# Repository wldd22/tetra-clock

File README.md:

# Tetra Clock

A custom alarm clock loosely based on the Blare guide.

## Details
PCB made using **KiCAD**<br>
Firmware uses **CircuitPython**

This PCB is a simple alarm clock display I designed to show the date and time, and set alarms.

- **Microcontroller**: XIAO ESP32-S3
- **Display**: 0.91 inch 128x32 OLED display (SSD1306 driver)
- **Sound**: 3V Active Electromagnetic Buzzer
- **Input**: Capacitive touchpads

**Features**:
- **ISO 8601 timestamp** datetime display
- Set **alarm time**
- **Alarm** enabled toggle
- **Snooze** enabled toggle

## About
When I saw [Mitxela's Precision Clock](https://mitxela.com/projects/precision_clock_mk_iv),
I was inspired to design a custom clock myself. I wanted mine to be much more compact, like
something you could carry around in a pocket, but that still looked cool and worked well.
I used capacitive pads because it's an easy way I've found to make button inputs that, one,
don't require any extra components, and two, are as compact as possible, being just as slim
as the board itself.

This project was originally made for week 1 (PCB week) of Hack Club's Half Life. The idea and some of
the components used were based on the [Blare guide](https://blare.hackclub.com/docs/getting-started),
but the actual design and the firmware was created from scratch by me.

## Setup
1. **Obtain hardware** - Buy [the **components**](BOM.csv) and get the **PCB** fabricated ([gerber](/production/gerber/gerber.zip)).
2. **Solder parts** - Using pin headers where necessary, solder the **microcontroller**, **buzzer**, and **display** onto the board.
3. **Install CircuitPython** - Use the [CircuitPython guide for the XIAO ESP32S3](https://wiki.seeedstudio.com/xiao_esp32s3_project_circuitpython/) to install it onto the board.
4. **Upload firmware** - Use the same guide to upload [the firmware](/firmware/code.py) to the board.

## Images

### Schematic

### PCB

## BOM

Item  | Description  | Quantity  | Source  | Cost  | Amount
--- | --- | --- | --- | --- | ---
Seeed Studio XIAO ESP32-S3  |  Microcontroller  |  1  |  [Robu](https://robu.in/product/seeed-studio-xiao-esp32s3-2-4ghz-wifi-ble-5-0/)  |  $12.00  |  $12.00
0.91 inch 128x32 Blue OLED Display Module  |  OLED Screen  |  1  |  [Robu](https://robu.in/product/0-91-inch-128x32-i2c-iic-serial-blue-oled-lcd-display-module/)  |  $2.20  |  $2.20
PCB  |  The board  |  1  |  [JLCPCB](https://jlcpcb.com/)  |  $4.00  |  $4.00
1X20P Machined Pin Header  |  Pin headers for the MCU and display  |  1  |  [Robu](https://robu.in/product/361030120sg111901-jiln-2-54x3-0machined-pin-header-1x20p-180-l11-96-upper-pinpoint0-60-bottom-pinpoint0-50-au1u-pps/)  |  $0.20  |  $0.20
3V Active Electromagnetic Buzzer  |  Buzzer  |  1  |  [Robu](https://robu.in/product/3v-active-electromagnetic-buzzer-pack-of-5/)  |  $0.25  |  $0.25
Estimated total shipping  |  -  |  1  |  -  |  -  |  $10.00
TOTAL  |  |  |  |  |  $28.65

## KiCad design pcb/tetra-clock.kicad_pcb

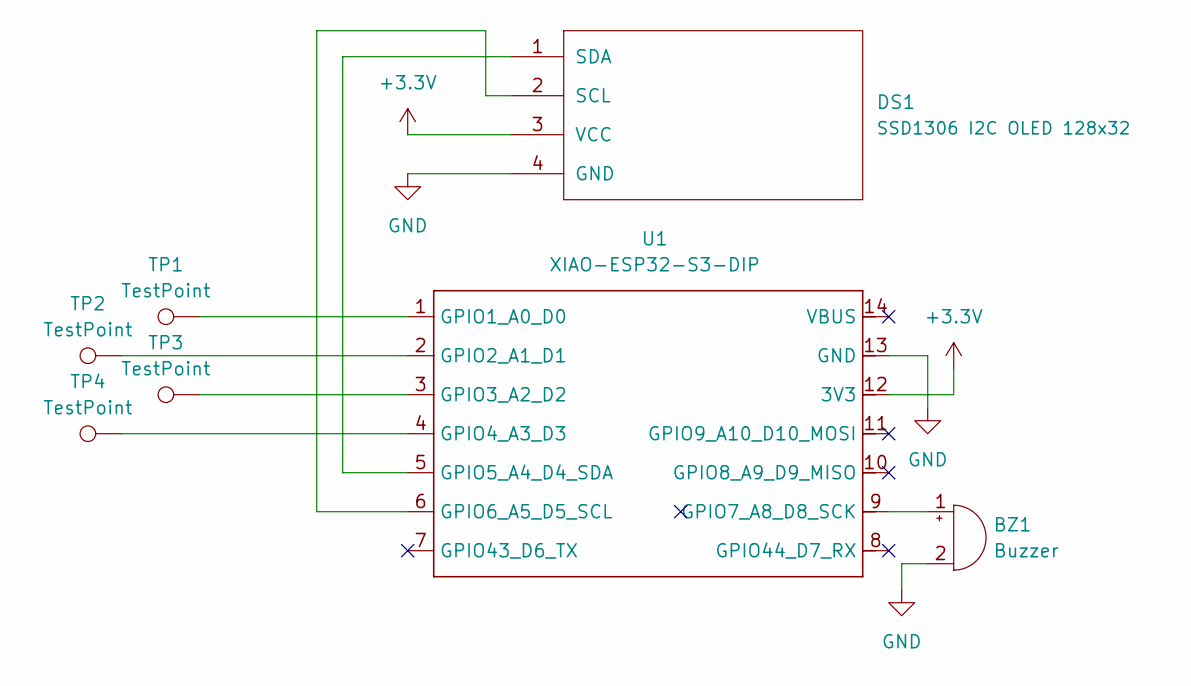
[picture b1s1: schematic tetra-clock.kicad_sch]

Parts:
BZ1: Buzzer; Buzzer_12x9.5RM7.6
DS1: SSD1306 I2C OLED 128x32
TP1, TP2, TP3, TP4: TestPoint; CAP_CIRCLE_PAD
U1: XIAO-ESP32-S3-DIP

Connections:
+3.3V: DS1.3 (VCC), U1.12 (3V3)
GND: BZ1.2 (-), DS1.4 (GND), U1.13 (GND)
unnamed: BZ1.1 (+), U1.9 (GPIO7_A8_D8_SCK)
unnamed: DS1.2 (SCL), U1.6 (GPIO6_A5_D5_SCL)
unnamed: DS1.1 (SDA), U1.5 (GPIO5_A4_D4_SDA)
unnamed: TP1.1 (1_1), U1.1 (GPIO1_A0_D0)
unnamed: TP2.1 (1_1), U1.2 (GPIO2_A1_D1)
unnamed: TP3.1 (1_1), U1.3 (GPIO3_A2_D2)
unnamed: TP4.1 (1_1), U1.4 (GPIO4_A3_D3)

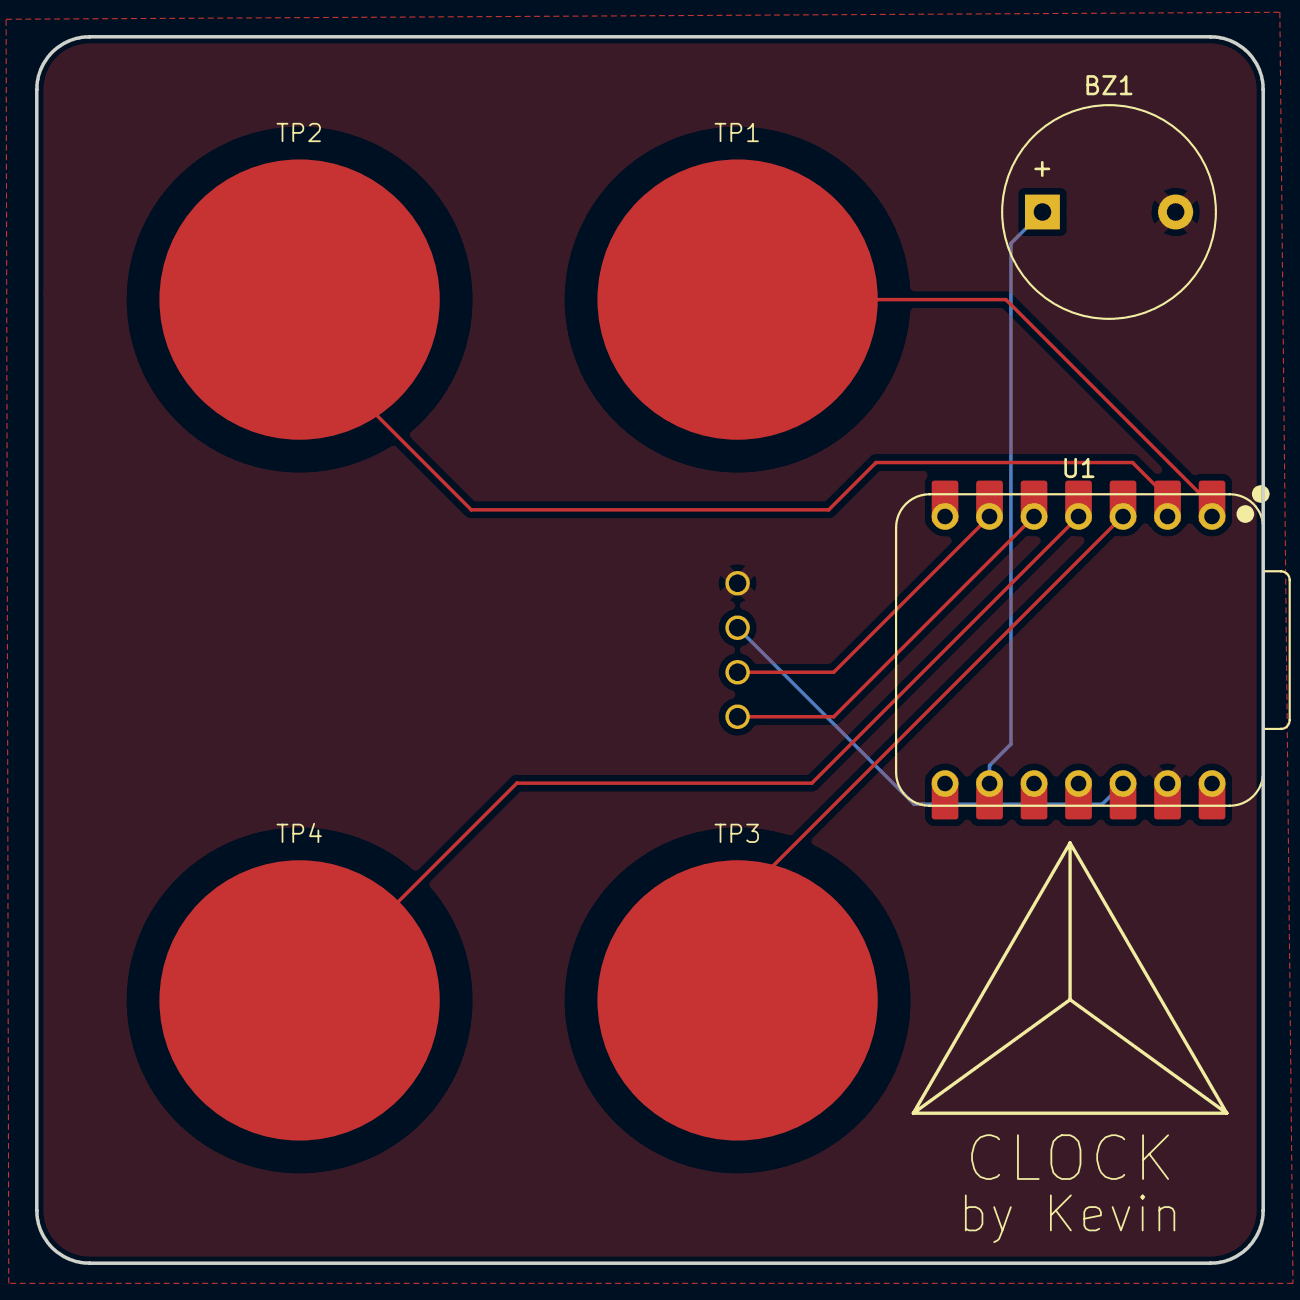
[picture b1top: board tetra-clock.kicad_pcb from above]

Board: 2 copper layers, 70.0 x 70.0 mm, 7 parts (0 on the bottom side), 9 nets.
